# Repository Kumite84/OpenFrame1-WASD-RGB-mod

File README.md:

# OpenFrame1-WASD-RGB-mod
modified version of OpenFrame1 with WASD layout and RGB powered by Fight Lights

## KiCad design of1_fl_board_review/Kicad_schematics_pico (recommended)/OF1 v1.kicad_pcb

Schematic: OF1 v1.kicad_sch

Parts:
D1: 1N5400; DO201-15
D2: 1N5819HW-7-F; SOD3715X145N
FL1, FL2, FL3, FL4, FL5, FL6, FL7, FL8, FL9, FL10, FL11, FL12, FL13, FL14, FL15, FL16, FL17, FL18, FL19, FL20, FL21, FL22, FL23, FL24, FL25, FL26, FL27, FL28, FL29, FL30, FL31, FL32, FL33, FL34, FL35, FL36, FL37, FL38, FL39, FL40, FL41, FL42, FL43, FL44, FL45, FL46: WS2812B; LED_WS2812B_PLCC4_5.0x5.0mm_P3.2mm; LCSC C2874885
J1, J6: RPI_PICO-TH; RPI_PICO_TH
J2: MOLEX2171830001; 24P
J3: MA06-1
J4: MA04-1
J5: GT-USB-7010; 16P
R1, R3: 5.1k; R_Axial_DIN0207_L6.3mm_D2.5mm_P7.62mm_Horizontal
R2, R4: 5.1k; R_0603_1608Metric
U$1, U$2, U$3, U$4, U$5, U$6, U$7, U$8, U$9, U$10, U$11, U$12, U$13, U$14, U$15, U$16, U$17, U$18, U$19, U$20, U$21, U$22, U$23: MX-B; MX-BOTH

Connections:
5V: FL1.1 (VDD), FL2.1 (VDD), FL3.1 (VDD), FL4.1 (VDD), FL5.1 (VDD), FL6.1 (VDD), FL7.1 (VDD), FL8.1 (VDD), FL9.1 (VDD), FL10.1 (VDD), FL11.1 (VDD), FL12.1 (VDD), FL13.1 (VDD), FL14.1 (VDD), FL15.1 (VDD), FL16.1 (VDD), FL17.1 (VDD), FL18.1 (VDD), FL19.1 (VDD), FL20.1 (VDD), FL21.1 (VDD), FL22.1 (VDD), FL23.1 (VDD), FL24.1 (VDD), FL25.1 (VDD), FL26.1 (VDD), FL27.1 (VDD), FL28.1 (VDD), FL29.1 (VDD), FL30.1 (VDD), FL31.1 (VDD), FL32.1 (VDD), FL33.1 (VDD), FL34.1 (VDD), FL35.1 (VDD), FL36.1 (VDD), FL37.1 (VDD), FL38.1 (VDD), FL39.1 (VDD), FL40.1 (VDD), FL41.1 (VDD), FL42.1 (VDD), FL43.1 (VDD), FL44.1 (VDD), FL45.1 (VDD), FL46.1 (VDD)
+5V: J1.VBUS, J2.A4 (A_VBUS), J2.A9 (A_VBUS), J2.B4 (B_VBUS), J2.B9 (B_VBUS), J3.6, J4.4, J5.A4/B9 (VBUS), J5.B4/A9 (VBUS), J6.VSYS
/A: J1.GP14, J6.GP14, U$20.P$2 (PIN1), U$20.P$3 (PIN1)
/B: J1.GP26_A0, J6.GP26_A0, U$13.P$2 (PIN1), U$13.P$3 (PIN1)
/C_DN: J1.GP15, J6.GP15, U$21.P$2 (PIN1), U$21.P$3 (PIN1)
/C_LT: J1.GP13, J6.GP13, U$18.P$2 (PIN1), U$18.P$3 (PIN1)
/C_RT: J1.GP16, J6.GP16, U$19.P$2 (PIN1), U$19.P$3 (PIN1)
/C_UP: J1.GP12, J6.GP12, U$17.P$2 (PIN1), U$17.P$3 (PIN1)
/D+: J1.TP3 (D-), J2.A6 (DA+), J2.B6 (DB+), J4.2, J5.A6 (D+), J5.B6 (D+)
/D-: J1.TP2 (D+), J2.A7 (DA-), J2.B7 (DB-), J4.3, J5.A7 (D-), J5.B7 (D-)
/DATA: J1.GP28_A2, J2.A11 (RX2+), J2.B11 (RX1+), J3.4
/DOWN: J1.GP3, J6.GP3, U$4.P$2 (PIN1), U$4.P$3 (PIN1)
/HOME: J1.GP11, J6.GP11, U$23.P$2 (PIN1), U$23.P$3 (PIN1)
/L: J1.GP5, J6.GP5, U$1.P$2 (PIN1), U$1.P$3 (PIN1)
/LEFT: J1.GP4, J6.GP4, U$2.P$2 (PIN1), U$2.P$3 (PIN1)
/LS: J1.GP20, J6.GP20, U$11.P$2 (PIN1), U$11.P$3 (PIN1)
/M1: J1.GP6, J6.GP6, U$6.P$2 (PIN1), U$6.P$3 (PIN1)
/M2: J1.GP7, J6.GP7, U$7.P$2 (PIN1), U$7.P$3 (PIN1)
/MS: J1.GP18, J6.GP18, U$12.P$2 (PIN1), U$12.P$3 (PIN1)
/R: J1.GP27_A1, J6.GP27_A1, U$9.P$2 (PIN1), U$9.P$3 (PIN1)
/RIGHT: J1.GP2, J6.GP2, U$5.P$2 (PIN1), U$5.P$3 (PIN1)
/SELECT: J1.GP10, J6.GP10, U$22.P$2 (PIN1), U$22.P$3 (PIN1)
/START: J1.GP0, J6.GP0, U$8.P$2 (PIN1), U$8.P$3 (PIN1)
/UP: J1.GP17, J6.GP17, U$16.P$2 (PIN1), U$16.P$3 (PIN1)
/W: J1.GP1, J6.GP1, U$3.P$2 (PIN1), U$3.P$3 (PIN1)
/X: J1.GP21, J6.GP21, U$14.P$2 (PIN1), U$14.P$3 (PIN1)
/Y: J1.GP22, J6.GP22, U$10.P$2 (PIN1), U$10.P$3 (PIN1)
/Z: J1.GP19, J6.GP19, U$15.P$2 (PIN1), U$15.P$3 (PIN1)
GND: FL1.3 (VSS), FL2.3 (VSS), FL3.3 (VSS), FL4.3 (VSS), FL5.3 (VSS), FL6.3 (VSS), FL7.3 (VSS), FL8.3 (VSS), FL9.3 (VSS), FL10.3 (VSS), FL11.3 (VSS), FL12.3 (VSS), FL13.3 (VSS), FL14.3 (VSS), FL15.3 (VSS), FL16.3 (VSS), FL17.3 (VSS), FL18.3 (VSS), FL19.3 (VSS), FL20.3 (VSS), FL21.3 (VSS), FL22.3 (VSS), FL23.3 (VSS), FL24.3 (VSS), FL25.3 (VSS), FL26.3 (VSS), FL27.3 (VSS), FL28.3 (VSS), FL29.3 (VSS), FL30.3 (VSS), FL31.3 (VSS), FL32.3 (VSS), FL33.3 (VSS), FL34.3 (VSS), FL35.3 (VSS), FL36.3 (VSS), FL37.3 (VSS), FL38.3 (VSS), FL39.3 (VSS), FL40.3 (VSS), FL41.3 (VSS), FL42.3 (VSS), FL43.3 (VSS), FL44.3 (VSS), FL45.3 (VSS), FL46.3 (VSS), J1.AGND, J1.GND@1 (GND), J1.GND@2 (GND), J1.GND@3 (GND), J1.GND@4 (GND), J1.GND@5 (GND), J1.GND@6 (GND), J1.GND@7 (GND), J1.GND@8 (GND), J2.A1 (GNDA), J2.A12 (GNDA), J2.B1 (GNDB), J2.B12 (GNDB), J2.SHIELD1 (SHIELD), J2.SHIELD2 (SHIELD), J2.SHIELD3 (SHIELD), J2.SHIELD4 (SHIELD), J3.1, J3.2, J4.1, J5.A1/B12 (GND), J5.B1/A12 (GND), J5.SHIELD1 (SHIELD), J5.SHIELD2 (SHIELD), J5.SHIELD3 (SHIELD), J5.SHIELD4 (SHIELD), J6.AGND, J6.GND@1 (GND), J6.GND@2 (GND), J6.GND@3 (GND), J6.GND@4 (GND), J6.GND@5 (GND), J6.GND@6 (GND), J6.GND@7 (GND), J6.GND@8 (GND), J6.GP8, R1.2, R2.2, R3.2, R4.2, U$1.P$1 (PIN2), U$1.P$4 (PIN2), U$2.P$1 (PIN2), U$2.P$4 (PIN2), U$3.P$1 (PIN2), U$3.P$4 (PIN2), U$4.P$1 (PIN2), U$4.P$4 (PIN2), U$5.P$1 (PIN2), U$5.P$4 (PIN2), U$6.P$1 (PIN2), U$6.P$4 (PIN2), U$7.P$1 (PIN2), U$7.P$4 (PIN2), U$8.P$1 (PIN2), U$8.P$4 (PIN2), U$9.P$1 (PIN2), U$9.P$4 (PIN2), U$10.P$1 (PIN2), U$10.P$4 (PIN2), U$11.P$1 (PIN2), U$11.P$4 (PIN2), U$12.P$1 (PIN2), U$12.P$4 (PIN2), U$13.P$1 (PIN2), U$13.P$4 (PIN2), U$14.P$1 (PIN2), U$14.P$4 (PIN2), U$15.P$1 (PIN2), U$15.P$4 (PIN2), U$16.P$1 (PIN2), U$16.P$4 (PIN2), U$17.P$1 (PIN2), U$17.P$4 (PIN2), U$18.P$1 (PIN2), U$18.P$4 (PIN2), U$19.P$1 (PIN2), U$19.P$4 (PIN2), U$20.P$1 (PIN2), U$20.P$4 (PIN2), U$21.P$1 (PIN2), U$21.P$4 (PIN2), U$22.P$1 (PIN2), U$22.P$4 (PIN2), U$23.P$1 (PIN2), U$23.P$4 (PIN2)
LED1: FL1.4 (DIN), J6.GP9
LED2: FL1.2 (DOUT), FL2.4 (DIN)
LED3: FL2.2 (DOUT), FL3.4 (DIN)
LED4: FL3.2 (DOUT), FL4.4 (DIN)
LED5: FL4.2 (DOUT), FL5.4 (DIN)
LED6: FL5.2 (DOUT), FL6.4 (DIN)
LED7: FL6.2 (DOUT), FL7.4 (DIN)
LED8: FL7.2 (DOUT), FL8.4 (DIN)
LED9: FL8.2 (DOUT), FL9.4 (DIN)
LED10: FL9.2 (DOUT), FL10.4 (DIN)
LED11: FL10.2 (DOUT), FL11.4 (DIN)
LED12: FL11.2 (DOUT), FL12.4 (DIN)
LED13: FL12.2 (DOUT), FL13.4 (DIN)
LED14: FL13.2 (DOUT), FL14.4 (DIN)
LED15: FL14.2 (DOUT), FL15.4 (DIN)
LED16: FL15.2 (DOUT), FL16.4 (DIN)
LED17: FL16.2 (DOUT), FL17.4 (DIN)
LED18: FL17.2 (DOUT), FL18.4 (DIN)
LED19: FL18.2 (DOUT), FL19.4 (DIN)
LED20: FL19.2 (DOUT), FL20.4 (DIN)
LED21: FL20.2 (DOUT), FL21.4 (DIN)
LED22: FL21.2 (DOUT), FL22.4 (DIN)
LED23: FL22.2 (DOUT), FL23.4 (DIN)
LED24: FL23.2 (DOUT), FL24.4 (DIN)
LED25: FL24.2 (DOUT), FL25.4 (DIN)
LED26: FL25.2 (DOUT), FL26.4 (DIN)
LED27: FL26.2 (DOUT), FL27.4 (DIN)
LED28: FL27.2 (DOUT), FL28.4 (DIN)
LED29: FL28.2 (DOUT), FL29.4 (DIN)
LED30: FL29.2 (DOUT), FL30.4 (DIN)
LED31: FL30.2 (DOUT), FL31.4 (DIN)
LED32: FL31.2 (DOUT), FL32.4 (DIN)
LED33: FL32.2 (DOUT), FL33.4 (DIN)
LED34: FL33.2 (DOUT), FL34.4 (DIN)
LED35: FL34.2 (DOUT), FL35.4 (DIN)
LED36: FL35.2 (DOUT), FL36.4 (DIN)
LED37: FL36.2 (DOUT), FL37.4 (DIN)
LED38: FL37.2 (DOUT), FL38.4 (DIN)
LED39: FL38.2 (DOUT), FL39.4 (DIN)
LED40: FL39.2 (DOUT), FL40.4 (DIN)
LED41: FL40.2 (DOUT), FL41.4 (DIN)
LED42: FL41.2 (DOUT), FL42.4 (DIN)
LED43: FL42.2 (DOUT), FL43.4 (DIN)
LED44: FL43.2 (DOUT), FL44.4 (DIN)
LED45: FL44.2 (DOUT), FL45.4 (DIN)
LED46: FL45.2 (DOUT), FL46.4 (DIN)
unnamed: J2.A5 (CC1), R1.1, R2.1
unnamed: J2.B5 (CC2), R3.1, R4.1
V+: D1.A, D2.A, J2.A2 (TX1+), J2.B2 (TX2+), J3.5
VCC: D1.C, D2.C (K), J1.VSYS, J3.3

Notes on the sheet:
USB Connector

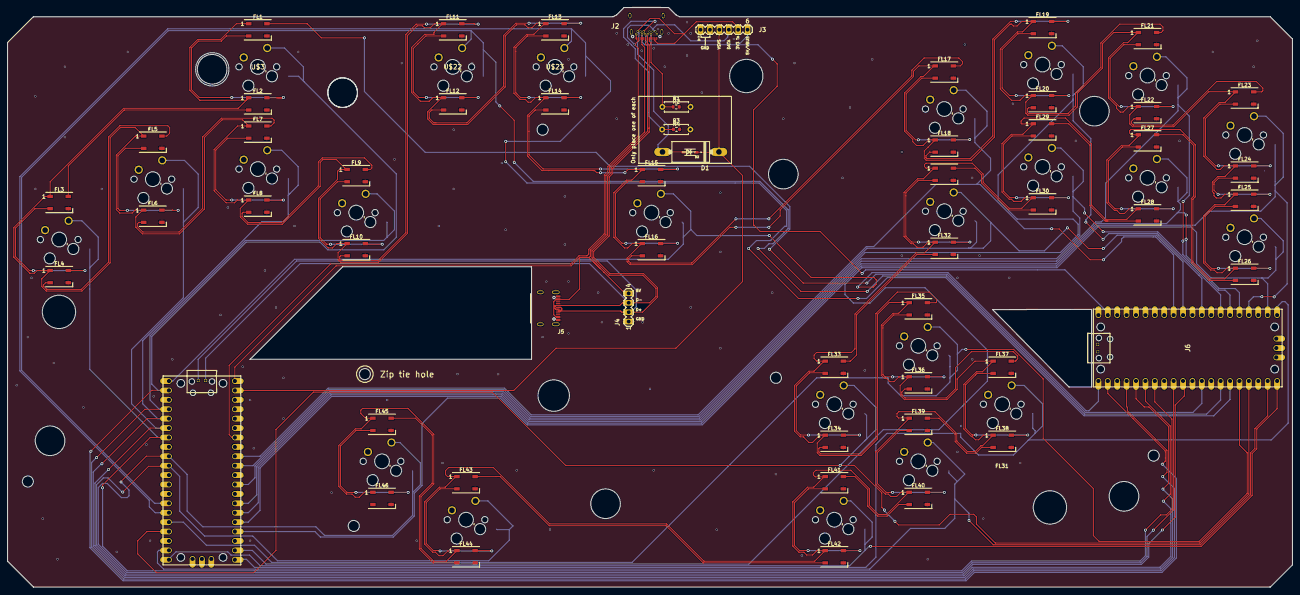
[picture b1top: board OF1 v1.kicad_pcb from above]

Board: 2 copper layers, 347.0 x 156.5 mm, 100 parts (0 on the bottom side), 79 nets.

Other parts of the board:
@HOLE0, @HOLE1, @HOLE2, @HOLE3, @HOLE4, @HOLE5, @HOLE6, @HOLE7, @HOLE7#2, @HOLE7#3, @HOLE8, @HOLE9, @HOLE10, @HOLE11, @HOLE12, @HOLE13, @HOLE14, @HOLE15, @HOLE16: (no value)

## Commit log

2023-12-07 submitted for board review
